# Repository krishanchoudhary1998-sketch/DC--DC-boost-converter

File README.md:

# DC-DC Boost Converter V1

A high-performance step-up DC-DC boost converter based on the **XL6009** switching regulator IC. Designed in KiCad.

[Circuit Design]

[PCB Top]

[PCB Bottom]

[PCB]

## Features

- Wide input voltage range (XL6009: 5V–32V)
- Adjustable output voltage via 50K trimmer potentiometer
- 33µH switching inductor
- 40V/3A Schottky diode (SS34) for rectification
- Input and output filtering capacitors
- Compact PCB layout with pin header connectors

## Specifications

| Parameter          | Value            |
|--------------------|------------------|
| Controller IC      | XL6009 (XLSEMI)  |
| Topology           | Boost (Step-Up)  |
| Inductor           | 33µH             |
| Switching Diode    | SS34 (40V, 3A)   |
| Input Capacitor    | 47µF / 50V       |
| Output Capacitor   | 220µF / 50V      |
| Ceramic Caps       | 1µF (x2)         |
| Feedback Resistor  | 1KΩ              |
| Voltage Adjust     | 50K trim pot      |
| Input Connector    | J1 (+), J2 (GND) |
| Output Connector   | J3 (+), J4 (GND) |

## Schematic

The circuit uses the XL6009 in its standard boost configuration. The feedback pin (FB) is connected to a voltage divider formed by a 1K resistor and a 50K trimmer potentiometer, allowing the output voltage to be adjusted.

## Design Files

- **Schematic:** `Boost Converter V1.kicad_sch`
- **PCB Layout:** `Boost Converter V1.kicad_pcb`
- **Project File:** `Boost Converter V1.kicad_pro`

## Output Voltage Adjustment

The output voltage is set by the feedback divider:

```
Vout = 1.25V x (1 + RV1 / R1)
```

Where R1 = 1KΩ and RV1 is the 50K trim pot. This provides a wide adjustable range.

## Author

**Krishan CHOUDHARY** — 2025

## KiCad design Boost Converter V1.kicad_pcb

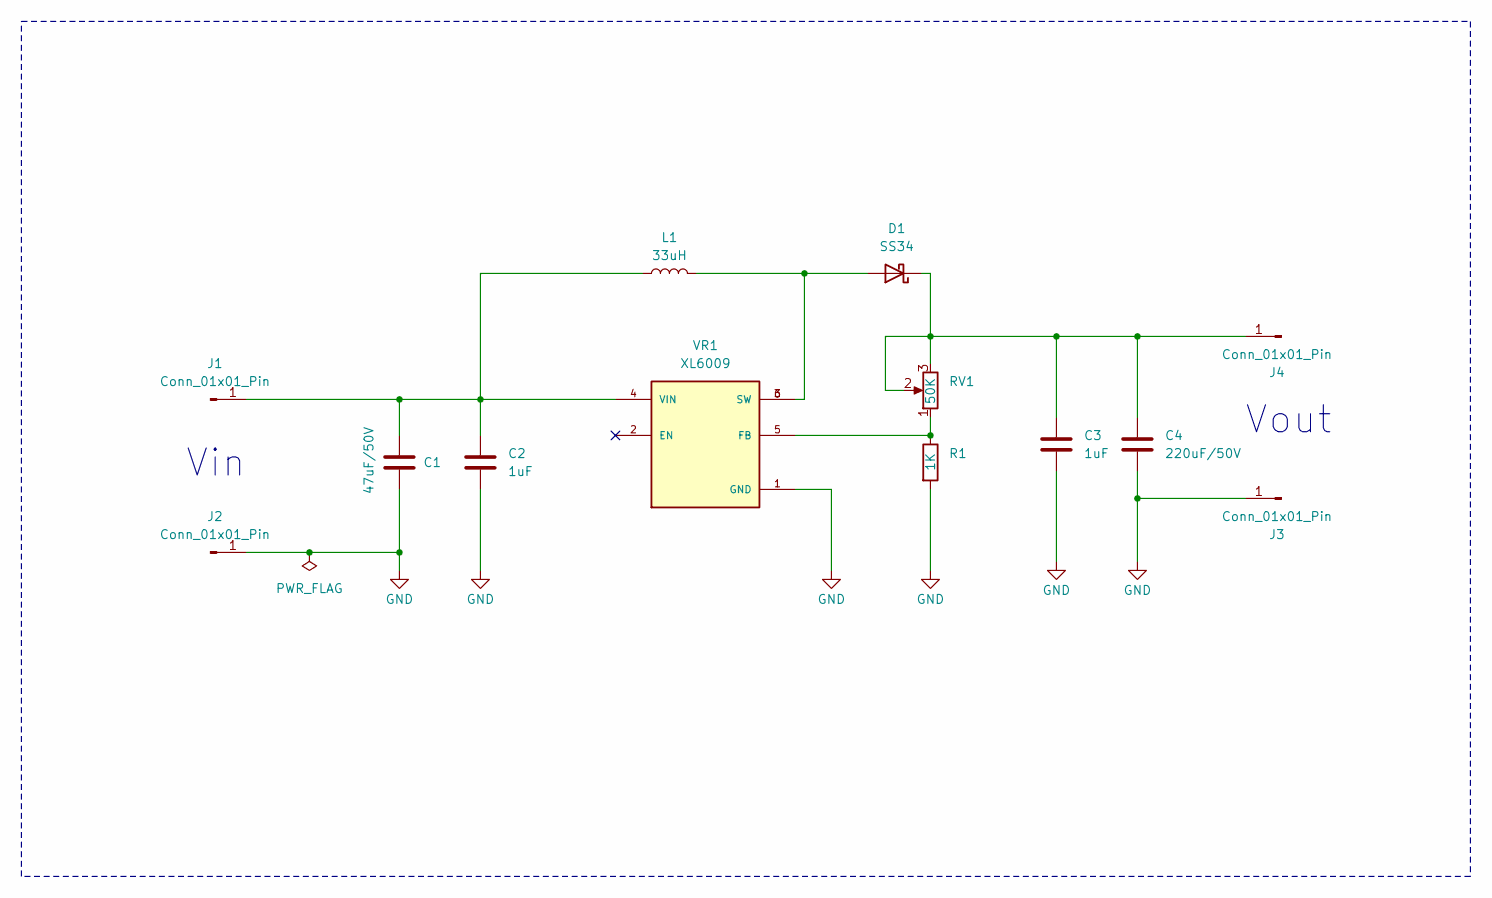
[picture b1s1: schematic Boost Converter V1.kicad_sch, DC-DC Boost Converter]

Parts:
C1: 47uF/50V; C_Radial_D6.3mm_H11.0mm_P2.50mm
C2, C3: 1uF; C_0805_2012Metric
C4: 220uF/50V; C_Radial_D6.3mm_H11.0mm_P2.50mm
D1: SS34; D_SMA
J1, J2, J3, J4: Conn_01x01_Pin; PinHeader_1x01_P2.54mm_Vertical
L1: 33uH; L_12x12mm_H8mm
R1: 1K; R_1206_3216Metric
RV1: 50K; Potentiometer_Bourns_3296W_Vertical
VR1: XL6009; PARTREV 1.1

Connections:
GND: C1.2, C2.2, C3.2, C4.2, J2.1, J3.1, R1.2, VR1.1 (GND)
unnamed: D1.2 (A), L1.2, VR1.3 (SW), VR1.6 (SW)
unnamed: C3.1, C4.1, D1.1 (K), J4.1, RV1.2, RV1.3
unnamed: C1.1, C2.1, J1.1, L1.1, VR1.4 (VIN)
unnamed: R1.1, RV1.1, VR1.5 (FB)

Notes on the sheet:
Vin
Vout

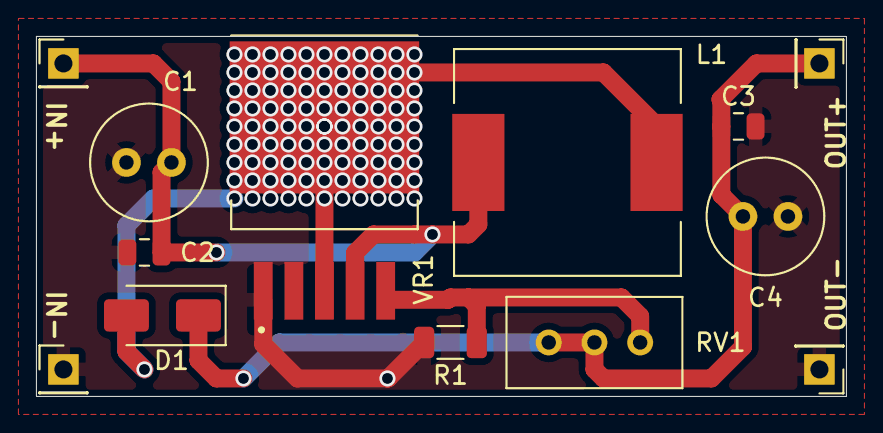
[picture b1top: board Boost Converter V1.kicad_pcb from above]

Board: 2 copper layers, 45.0 x 20.0 mm, 13 parts (0 on the bottom side), 5 nets.

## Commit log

2026-05-24 Update README with project details and specifications
    Added detailed project information, specifications, and features for the DC-DC boost converter.
2026-05-24 Fix image syntax in README.md
2026-05-24 Fix image formatting in README.md
    Updated image formatting for circuit and PCB designs in README.
2026-05-24 Create Docs
